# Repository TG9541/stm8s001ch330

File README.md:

# STM8S001J3M3 with CH330N USB Serial Dongle 

<a href="https://oshpark.com/shared_projects/cjOgBYNw"></img></a>

This is a design for an easy to use and easy to make key-chain sized STM8S001J3M3 dongle with CH330N USB-UART, e.g. for [STM8 eForth](https://github.com/TG9541/stm8ef) (which turns it into an interactive development environment). It can also be for interfacing, e.g., 1Wire or I2C sensors, as an IR-code transmitter, or prototyping software for "Low density" STM8S µCs (which all have 8K Flash, 1K RAM and 128-640 bytes EEPROM). If you're an 8bit computing and retro-computing affectionado: the typical performance is like a "6502 @ >20MHz" and it's about as easy to program.

The STM8S001J3M3 UART works in "half-duplex" mode (`PD5/UART_TX`) with the CH330N USB-UART in wired-or configuration (D1). The internal pull-up of `PD5` should be active (the STM8 eForth [STM8S001J3](https://github.com/TG9541/stm8ef/tree/master/STM8S001J3) base image takes care of that). This configuration allows IAP (in application programming) in Forth and ICP (in circuit programming) through `PD1/SWIM` through pin8 of the µC.

All components, including the PCB and the SMD USB-A connector are easy to obtain (e.g. [here](https://www.aliexpress.com/item/32900067411.html) for the USB connector - refer to the BOM is in the docs folder).

### Signals on Header J2

J2 provides the following signals:

Pin|Label|Pin STM8S001|GPIO|Features
-|-|-|-|-
1|5V|4|VDD|5V from USB or external supply
2|GND|2|VSS|GND
3|SDA|5|PB5 | I2C_SDA w/ 4k7 pull-up
-||5|PA3 | TIM2_CH3, [SPI_NSS], [UART1_TX]
4|SCL|6|PB4 | I2C_SCL w/ 4k7 pull-up, [ADC_ETR]
5|LSS| |PC3| NPN "Low Side" switch w/ 47R, e.g. IR LED @ 100mA
6|PC3|7|PC3 | TIM1_CH3, [TLI], [TIM1_CH1N] same as LS NPN base
-||7|PC4 | TIM1_CH4, CLK_CCO, AIN2, [TIM1_CH3]
-||7|PC5 | SPI_SCK, [TIM2_CH1]
7|SWIM|8|PD1 | SWIM
-||8|PC6 | SPI_MOSI, [TIM1_CH1]
-||8|PD3 | TIM2_CH2, TIM2_CH2, ADC_ETR
-||8|PD5 | UART1_TX, AIN5
8|PD6|1|PD6| UART1_RX, AIN6
-||1|PA1|[OSC_IN]
 
Note: the circuit relies on the USB port short-circuit protection!

### Example use-cases

* Pins 1, 2, 3 and 4 can be used for testing I2C modules w/ 5V supply (e.g. [STM8 eForth I2C Master](https://gist.github.com/TG9541/5c3405320794d91ef8129734a4bfc880#gistcomment-3565181))
* Pins 1 and 5 can be used for a 100mA IR LED (e.g. [IR Remote Control](https://gist.github.com/TG9541/40b811c3a611eb02ba9e3693f99222ac))
* Pins 1, 2 and 8 can be used for connecting an IR receiver
* Pins 1, 2 and 3 can control a [WS2812 LED strip](https://gist.github.com/TG9541/1761fa86b425a0c909b7bd1cc8017c2b)
* Pin 3 and can be used for RS485 after remapping the UART to PA3 (e.g. using the Forth SWIMCOM binary)
* [Learn programming Forth ...](https://github.com/TG9541/stm8ef/wiki/STM8-eForth-Programming)

### Populating the PCB

Populating the PCB by hand is easy. I recommend starting with D1, then U1, U2, C1 and C2. On the front side populate Q1 and the passive components first, then J1 and finally J2. 

The following components are optional (e.g. if J2 isn't needed): R1, R2, R3, R4, Q1 and J2.

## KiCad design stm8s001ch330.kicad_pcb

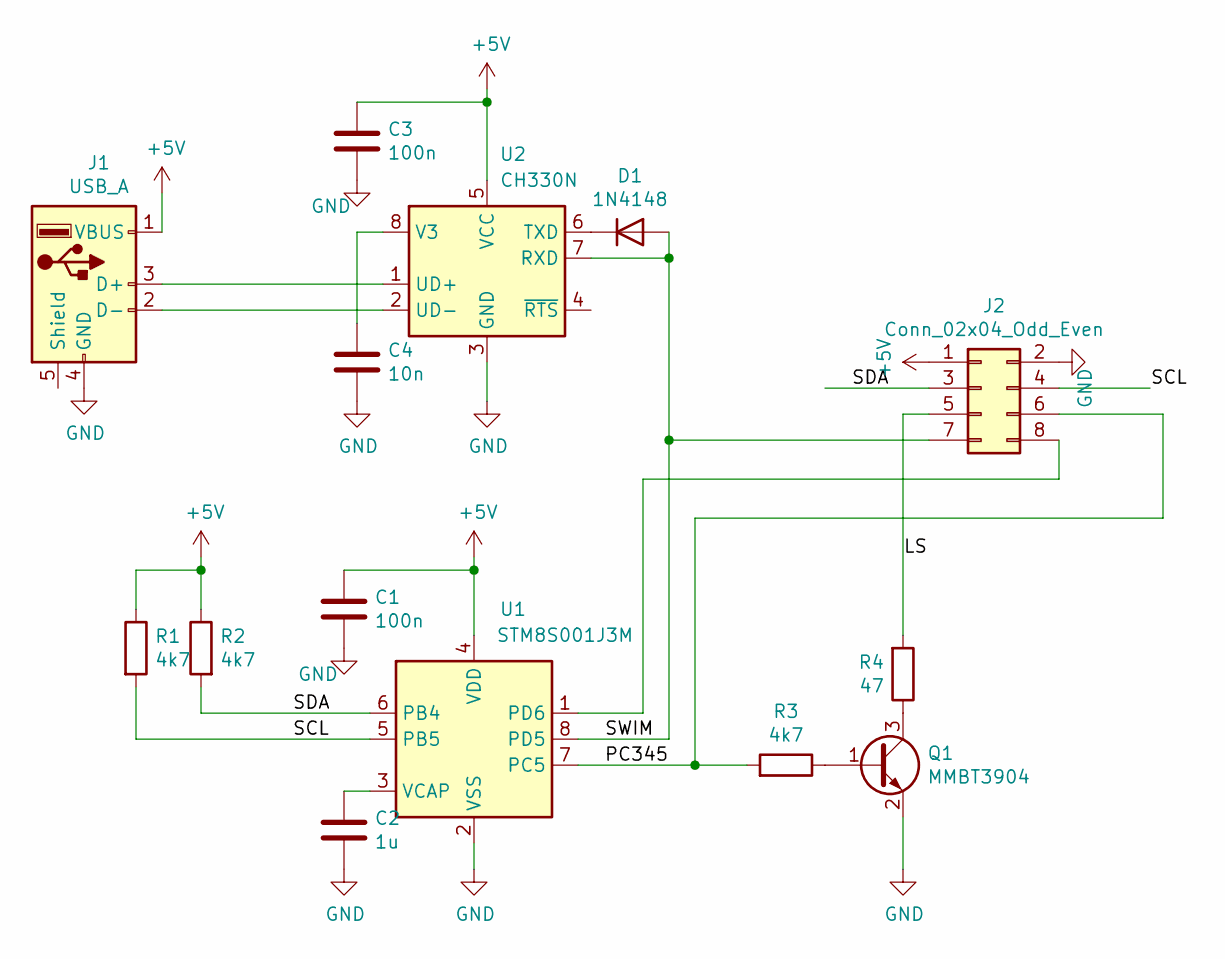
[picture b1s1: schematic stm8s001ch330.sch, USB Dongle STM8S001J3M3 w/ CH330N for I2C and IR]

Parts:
C1, C3: 100n; C_0603_1608Metric
C2: 1u; C_0603_1608Metric
C4: 10n; C_0603_1608Metric
D1: 1N4148; D_MiniMELF
J1: USB_A; USB_A_CNCTech_1001-011-01101_Horizontal
J2: Conn_02x04_Odd_Even; PinHeader_2x04_P2.54mm_Horizontal
Q1: MMBT3904; SOT-23
R1, R2, R3: 4k7; R_0603_1608Metric
R4: 47; R_0603_1608Metric
U1: STM8S001J3M; SOIC-8_3.9x4.9mm_P1.27mm
U2: CH330N; SOIC-8_3.9x4.9mm_P1.27mm

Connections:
+5V: C1.1, C3.1, J1.1 (VBUS), J2.1, R1.1, R2.1, U1.4 (VDD), U2.5 (VCC)
/LS: J2.5, R4.2
/PC345: J2.6, R3.2, U1.7 (PC5)
/SCL: J2.4, R1.2, U1.5 (PB5)
/SDA: J2.3, R2.2, U1.6 (PB4)
/SWIM: D1.2 (A), J2.7, U1.8 (PD5), U2.7 (RXD)
GND: C1.2, C2.2, C3.2, C4.2, J1.4 (GND), J2.2, Q1.2 (E), U1.2 (VSS), U2.3 (GND)
unnamed: C2.1, U1.3 (VCAP)
unnamed: C4.1, U2.8 (V3)
unnamed: D1.1 (K), U2.6 (TXD)
unnamed: J1.2 (D-), U2.2 (UD-)
unnamed: J1.3 (D+), U2.1 (UD+)
unnamed: J2.8, U1.1 (PD6)
unnamed: Q1.1 (B), R3.1
unnamed: Q1.3 (C), R4.1

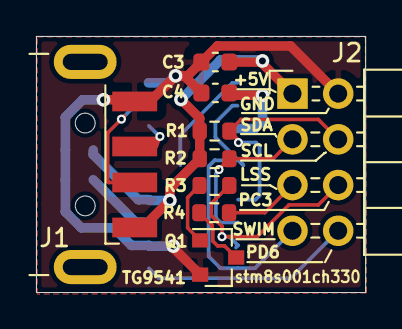
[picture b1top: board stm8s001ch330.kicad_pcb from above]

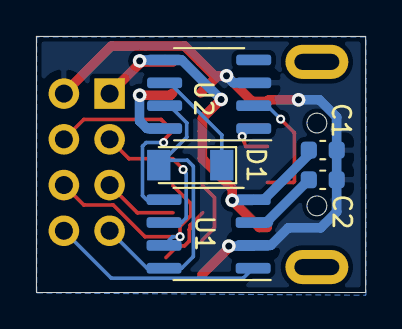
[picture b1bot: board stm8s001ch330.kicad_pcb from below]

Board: 2 copper layers, 18.3 x 14.2 mm, 14 parts (5 on the bottom side), 15 nets.

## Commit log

2020-12-26 Update README.md
    OSHPark badge added
2020-12-27 BOM added
2020-12-27 CSV files not excluded
